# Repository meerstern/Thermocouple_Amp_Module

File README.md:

# 熱電対センサアンプ基板
Thermocouple_Amp_Module with MAX31855K & STM32G030F6P6

## 概要
  * [MAX31855K][1]を使用したK型熱電対センサ用のアンプ基板です  
  * K型熱電対の温度に応じてアナログ出力(0~3.3V)を得ることが可能です  
  * JP1のOpenでローゲインモード(既定)、Closeでハイゲインモードの切替が可能です  
  * ローゲインモードの場合、ゲイン200℃/V、オフセット1.25Vで、温度範囲は-240℃～400℃です  
  * ハイゲインモードの場合、ゲイン400℃/V、オフセット1.25Vで、温度範囲は-270℃～800℃です  

  * 計算式  $K型熱電対温度 ℃ ＝ ゲイン × (電圧出力-オフセット)$  

 * 電源投入直後及び熱電対の断線や短絡等の異常時は基板上のエラーLED(赤色)が点灯します  
 * STM32G030F6P6マイコンのコードを公開しているため、ゲインやオフセットを変更することが可能です  
 * アナログ出力はマイコンのPWM出力(16bit)からローパスフィルタとバッファを介して出力しています  
 * 電源電圧が5Vであってもアナログ出力範囲は0~3.3Vです  
 * 変換精度±4℃、最大±6℃  
 * アナログ出力範囲の上限及び下限ではオフセット電圧や飽和電圧の影響で温度精度が低下する場合があります  
 * 電源電圧が3.3Vより低い場合、アナログ出力が低下する場合があります  
 * ファーム書き換えはSTLink及びSTM32CubeProgrammerが別途必要です  
 * 電源電圧：3.3V~5V  
 * 基板サイズ25mm x35mm、M3x2 幅19mm  
 
 ## 販売サイト
  * [スイッチサイエンス][2]

[1]: https://www.maximintegrated.com/jp/products/interface/sensor-interface/MAX31855.html
[2]: https://www.switch-science.com/products/8651

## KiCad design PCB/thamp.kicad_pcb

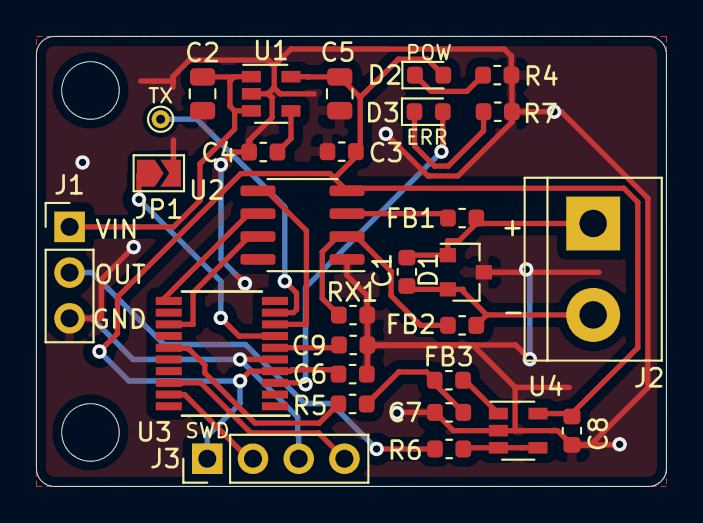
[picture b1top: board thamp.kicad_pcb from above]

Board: 2 copper layers, 35.0 x 25.0 mm, 31 parts (0 on the bottom side), 24 nets.

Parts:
C1, C4: 0.01u; C_0603_1608Metric
C2, C5: 10u; C_0805_2012Metric
C3, C6, C7, C8, C9: 0.1u; C_0603_1608Metric
D1: NUP2105L; SOT-23
D2: POW; LED_0603_1608Metric
D3: ERR; LED_0603_1608Metric
FB1, FB2, FB3: 470ohm; L_0603_1608Metric
J1: Conn_01x03; PinHeader_1x03_P2.54mm_Vertical
J2: Thermocouple; TerminalBlock_bornier-2_P5.08mm
J3: SWD; PinHeader_1x04_P2.54mm_Vertical
JP1: SW_DIP_x01; SolderJumper-2_P1.3mm_Open_TrianglePad1.0x1.5mm
R4, R7: 2.1k; R_0603_1608Metric
R5: 51k; R_0603_1608Metric
R6: 10; R_0603_1608Metric
REF1, REF2: MountingHole_3.2mm_M3
RX1: 0; R_0603_1608Metric
TP1: TestPoint; TestPoint_THTPad_D1.0mm_Drill0.5mm
U1: LD3985M33R_SOT23; SOT-23-5
U2: MAX31855KASA; SOIC-8_3.9x4.9mm_P1.27mm
U3: STM32G030F; TSSOP-20_4.4x6.5mm_P0.65mm
U4: LM321; SOT-23-5

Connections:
+3V3: C3.1, C5.1, C6.1, C8.1, D2.2, J3.1, U1.5, U2.4, U3.4, U4.5
/CS: U2.6, U3.11
/ERR: D3.2, U3.3
/MISO: U2.7, U3.13
/MODE: JP1.1, U3.7
/OUT: J1.2, R6.2
/PWM: R5.1, U3.15
/RST: C9.1, U3.6
/SCK: U2.5, U3.8
/SWCLK: J3.2, U3.19
/SWDIO: J3.4, U3.18
/TX: TP1.1, U3.9
/VIN: C2.1, J1.1, U1.1, U1.3
GND: C2.2, C3.2, C4.2, C5.2, C6.2, C7.2, C8.2, C9.2, D1.3, J1.3, J3.3, JP1.2, R4.2, R7.2, RX1.2, U1.2, U2.1, U3.5, U4.2
unnamed: C1.1, D1.1, FB1.2, J2.1
unnamed: C1.2, D1.2, FB2.2, J2.2
unnamed: C4.1, U1.4
unnamed: C7.1, FB3.2, R5.2
unnamed: D2.1, R4.1
unnamed: D3.1, R7.1
unnamed: FB1.1, U2.3
unnamed: FB2.1, RX1.1, U2.2
unnamed: FB3.1, U4.1
unnamed: R6.1, U4.3, U4.4

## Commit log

2022-11-15 Add images
2022-11-17 Add PCB Data
2022-11-17 Add Firmware
2022-11-21 Fix Firmware
2022-12-06 Add shop link
